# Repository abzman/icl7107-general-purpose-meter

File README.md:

# icl7107-general-purpose-meter

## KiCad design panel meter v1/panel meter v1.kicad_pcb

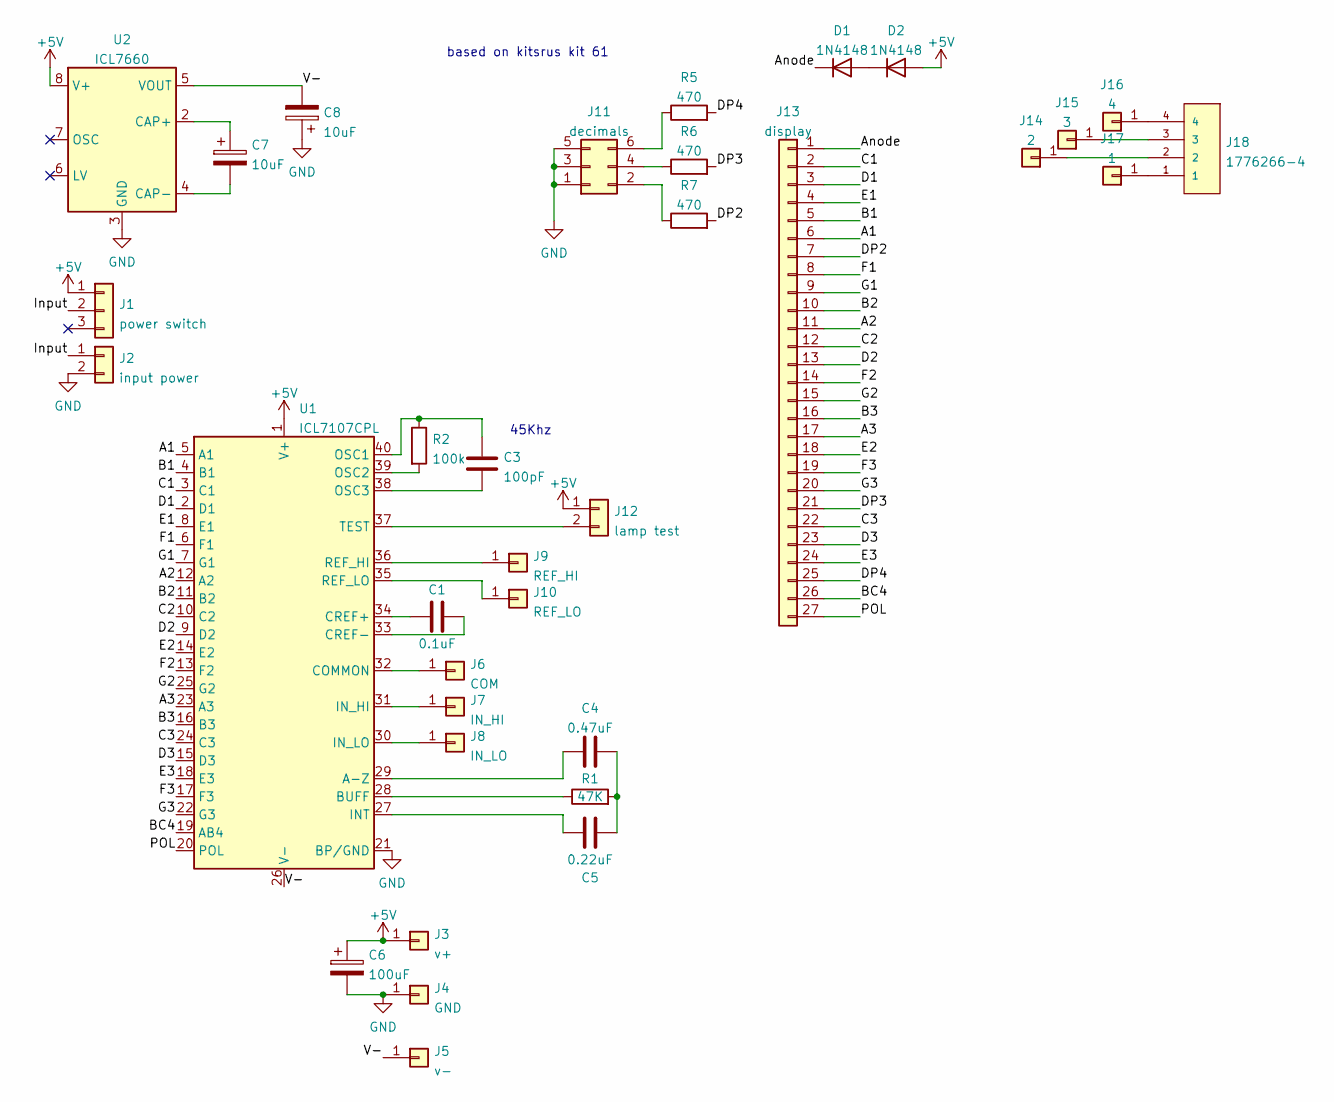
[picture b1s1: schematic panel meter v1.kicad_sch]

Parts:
C1: 0.1uF; C_Disc_D3.0mm_W1.6mm_P2.50mm
C3: 100pF; C_Disc_D3.0mm_W1.6mm_P2.50mm
C4: 0.47uF; C_Disc_D4.3mm_W1.9mm_P5.00mm
C5: 0.22uF; C_Disc_D4.3mm_W1.9mm_P5.00mm
C6: 100uF; CP_Radial_D6.3mm_P2.50mm
C7, C8: 10uF; CP_Radial_D4.0mm_P2.00mm
D1, D2: 1N4148; D_DO-35_SOD27_P7.62mm_Horizontal
J1: power switch; PinSocket_1x03_P2.54mm_Vertical
J2: input power; PinSocket_1x02_P2.54mm_Vertical
J3: v+; Pin_D1.0mm_L10.0mm
J4: GND; Pin_D1.0mm_L10.0mm
J5: v-; Pin_D1.0mm_L10.0mm
J6: COM; Pin_D1.0mm_L10.0mm
J7: IN_HI; Pin_D1.0mm_L10.0mm
J8: IN_LO; Pin_D1.0mm_L10.0mm
J9: REF_HI; Pin_D1.0mm_L10.0mm
J10: REF_LO; Pin_D1.0mm_L10.0mm
J11: decimals; PinHeader_2x03_P2.54mm_Vertical
J12: lamp test; PinHeader_1x02_P2.54mm_Vertical
J13: display; PinHeader_1x27_P2.54mm_Horizontal
J14: 2; Pin_D1.0mm_L10.0mm
J15: 3; Pin_D1.0mm_L10.0mm
J16: 4; Pin_D1.0mm_L10.0mm
J17: 1; Pin_D1.0mm_L10.0mm
J18: 1776266-4; TE_1776266-4
R1: 47K; R_Axial_DIN0207_L6.3mm_D2.5mm_P10.16mm_Horizontal
R2: 100k; R_Axial_DIN0207_L6.3mm_D2.5mm_P10.16mm_Horizontal
R5, R6, R7: 470; R_Axial_DIN0207_L6.3mm_D2.5mm_P2.54mm_Vertical
U1: ICL7107CPL; DIP-40_W15.24mm
U2: ICL7660; TSSOP-8_4.4x3mm_P0.65mm

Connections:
+5V: C6.1, D2.2 (A), J1.1, J3.1, J12.1, U1.1 (V+), U2.8 (V+)
/A1: J13.6, U1.5 (A1)
/A2: J13.11, U1.12 (A2)
/A3: J13.17, U1.23 (A3)
/Anode: D1.1 (K), J13.1
/B1: J13.5, U1.4 (B1)
/B2: J13.10, U1.11 (B2)
/B3: J13.16, U1.16 (B3)
/BC4: J13.26, U1.19 (AB4)
/C1: J13.2, U1.3 (C1)
/C2: J13.12, U1.10 (C2)
/C3: J13.22, U1.24 (C3)
/D1: J13.3, U1.2 (D1)
/D2: J13.13, U1.9 (D2)
/D3: J13.23, U1.15 (D3)
/DP2: J13.7, R7.2
/DP3: J13.21, R6.2
/DP4: J13.25, R5.2
/E1: J13.4, U1.8 (E1)
/E2: J13.18, U1.14 (E2)
/E3: J13.24, U1.18 (E3)
/F1: J13.8, U1.6 (F1)
/F2: J13.14, U1.13 (F2)
/F3: J13.19, U1.17 (F3)
/G1: J13.9, U1.7 (G1)
/G2: J13.15, U1.25 (G2)
/G3: J13.20, U1.22 (G3)
/Input: J1.2, J2.1
/POL: J13.27, U1.20 (POL)
/V-: C8.2, J5.1, U1.26 (V-), U2.5 (VOUT)
GND: C6.2, C8.1, J2.2, J4.1, J11.1, J11.3, J11.5, U1.21 (BP/GND), U2.3 (GND)
unnamed: C1.1, U1.34 (CREF+)
unnamed: C1.2, U1.33 (CREF-)
unnamed: C3.1, R2.1, U1.40 (OSC1)
unnamed: C3.2, U1.38 (OSC3)
unnamed: C4.1, U1.29 (A-Z)
unnamed: C4.2, C5.2, R1.2
unnamed: C5.1, U1.27 (INT)
unnamed: C7.1, U2.2 (CAP+)
unnamed: C7.2, U2.4 (CAP-)
unnamed: D1.2 (A), D2.1 (K)
unnamed: J14.1, J18.2
unnamed: J15.1, J18.3
unnamed: J16.1, J18.4
unnamed: J17.1, J18.1
unnamed: R1.1, U1.28 (BUFF)
unnamed: R2.2, U1.39 (OSC2)
unnamed: J11.6, R5.1
unnamed: J11.4, R6.1
unnamed: J11.2, R7.1
unnamed: J8.1, U1.30 (IN_LO)
unnamed: J7.1, U1.31 (IN_HI)
unnamed: J6.1, U1.32 (COMMON)
unnamed: J10.1, U1.35 (REF_LO)
unnamed: J9.1, U1.36 (REF_HI)
unnamed: J12.2, U1.37 (TEST)

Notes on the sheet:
45Khz
based on kitsrus kit 61

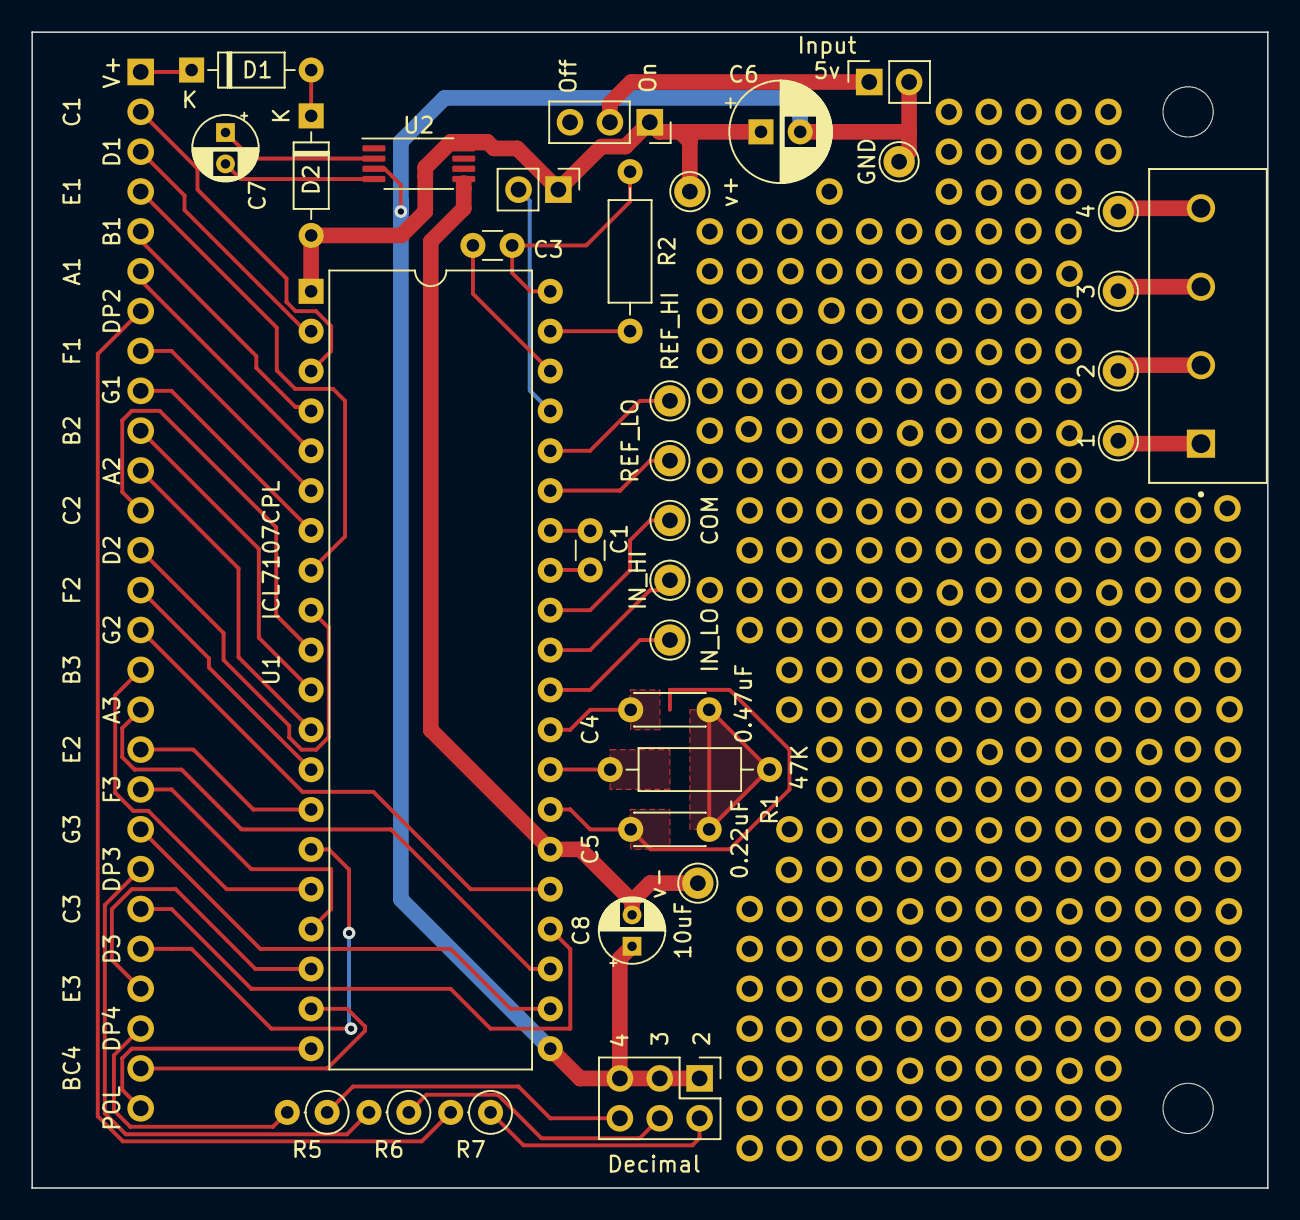
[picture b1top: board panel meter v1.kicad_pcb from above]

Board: 2 copper layers, 78.7 x 73.7 mm, 34 parts (1 on the bottom side), 56 nets.

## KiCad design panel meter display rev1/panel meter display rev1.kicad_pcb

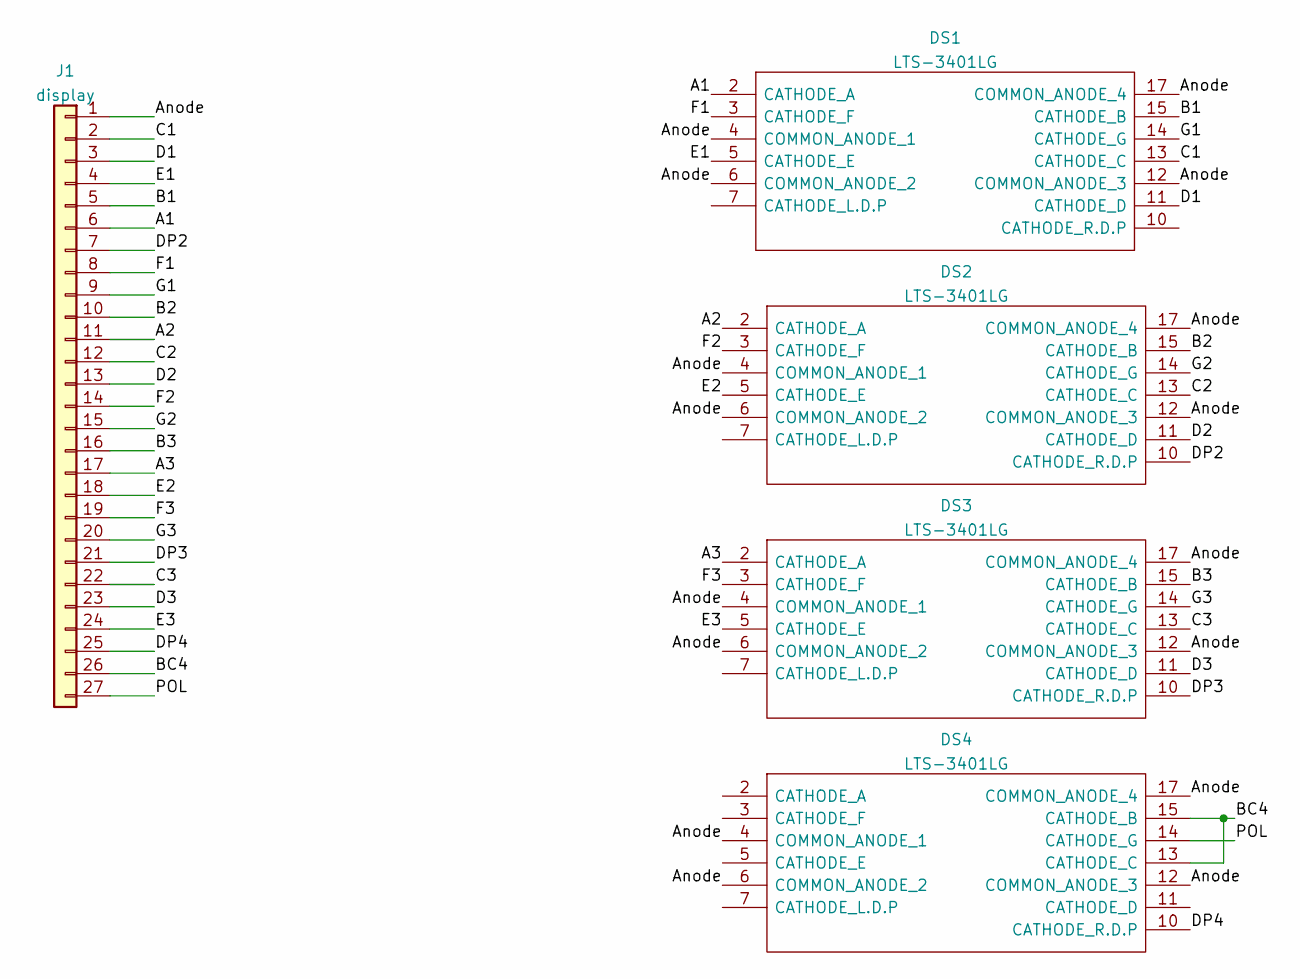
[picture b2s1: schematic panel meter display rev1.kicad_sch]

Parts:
DS1, DS2, DS3, DS4: LTS-3401LG; LTS3401LG; Mouser Part Number 859-LTS-3401LG
J1: display; PinHeader_1x27_P2.54mm_Vertical

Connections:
/A1: DS1.2 (CATHODE_A), J1.6
/A2: DS2.2 (CATHODE_A), J1.11
/A3: DS3.2 (CATHODE_A), J1.17
/Anode: DS1.4 (COMMON_ANODE_1), DS1.6 (COMMON_ANODE_2), DS1.12 (COMMON_ANODE_3), DS1.17 (COMMON_ANODE_4), DS2.4 (COMMON_ANODE_1), DS2.6 (COMMON_ANODE_2), DS2.12 (COMMON_ANODE_3), DS2.17 (COMMON_ANODE_4), DS3.4 (COMMON_ANODE_1), DS3.6 (COMMON_ANODE_2), DS3.12 (COMMON_ANODE_3), DS3.17 (COMMON_ANODE_4), DS4.4 (COMMON_ANODE_1), DS4.6 (COMMON_ANODE_2), DS4.12 (COMMON_ANODE_3), DS4.17 (COMMON_ANODE_4), J1.1
/B1: DS1.15 (CATHODE_B), J1.5
/B2: DS2.15 (CATHODE_B), J1.10
/B3: DS3.15 (CATHODE_B), J1.16
/BC4: DS4.13 (CATHODE_C), DS4.15 (CATHODE_B), J1.26
/C1: DS1.13 (CATHODE_C), J1.2
/C2: DS2.13 (CATHODE_C), J1.12
/C3: DS3.13 (CATHODE_C), J1.22
/D1: DS1.11 (CATHODE_D), J1.3
/D2: DS2.11 (CATHODE_D), J1.13
/D3: DS3.11 (CATHODE_D), J1.23
/DP2: DS2.10 (CATHODE_R.D.P), J1.7
/DP3: DS3.10 (CATHODE_R.D.P), J1.21
/DP4: DS4.10 (CATHODE_R.D.P), J1.25
/E1: DS1.5 (CATHODE_E), J1.4
/E2: DS2.5 (CATHODE_E), J1.18
/E3: DS3.5 (CATHODE_E), J1.24
/F1: DS1.3 (CATHODE_F), J1.8
/F2: DS2.3 (CATHODE_F), J1.14
/F3: DS3.3 (CATHODE_F), J1.19
/G1: DS1.14 (CATHODE_G), J1.9
/G2: DS2.14 (CATHODE_G), J1.15
/G3: DS3.14 (CATHODE_G), J1.20
/POL: DS4.14 (CATHODE_G), J1.27

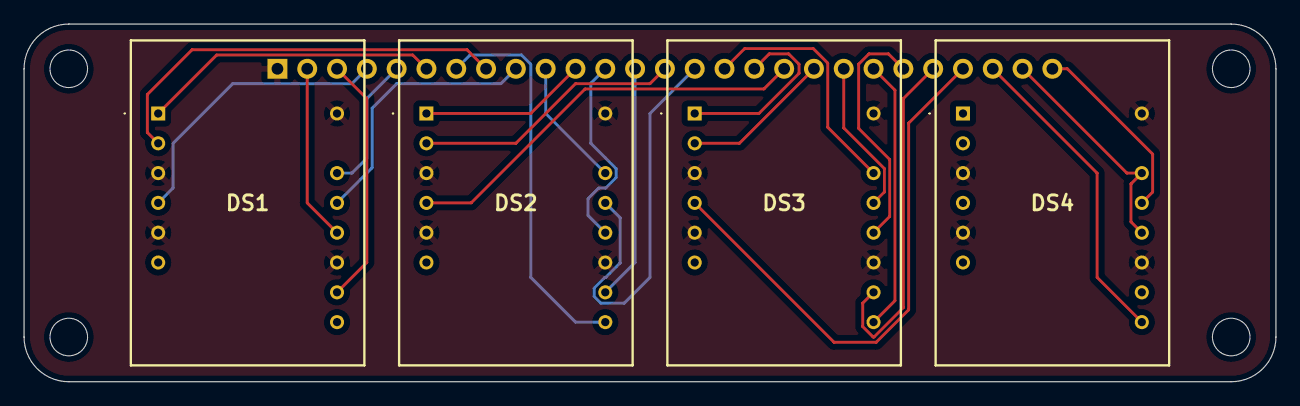
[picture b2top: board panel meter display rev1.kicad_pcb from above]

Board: 2 copper layers, 106.7 x 30.5 mm, 5 parts (1 on the bottom side), 27 nets.

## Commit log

2022-02-12 added display board
2022-03-14 gerber zip
2022-04-18 tweaked silk
